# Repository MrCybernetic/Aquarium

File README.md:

# Aquarium
My overengineered aquarium

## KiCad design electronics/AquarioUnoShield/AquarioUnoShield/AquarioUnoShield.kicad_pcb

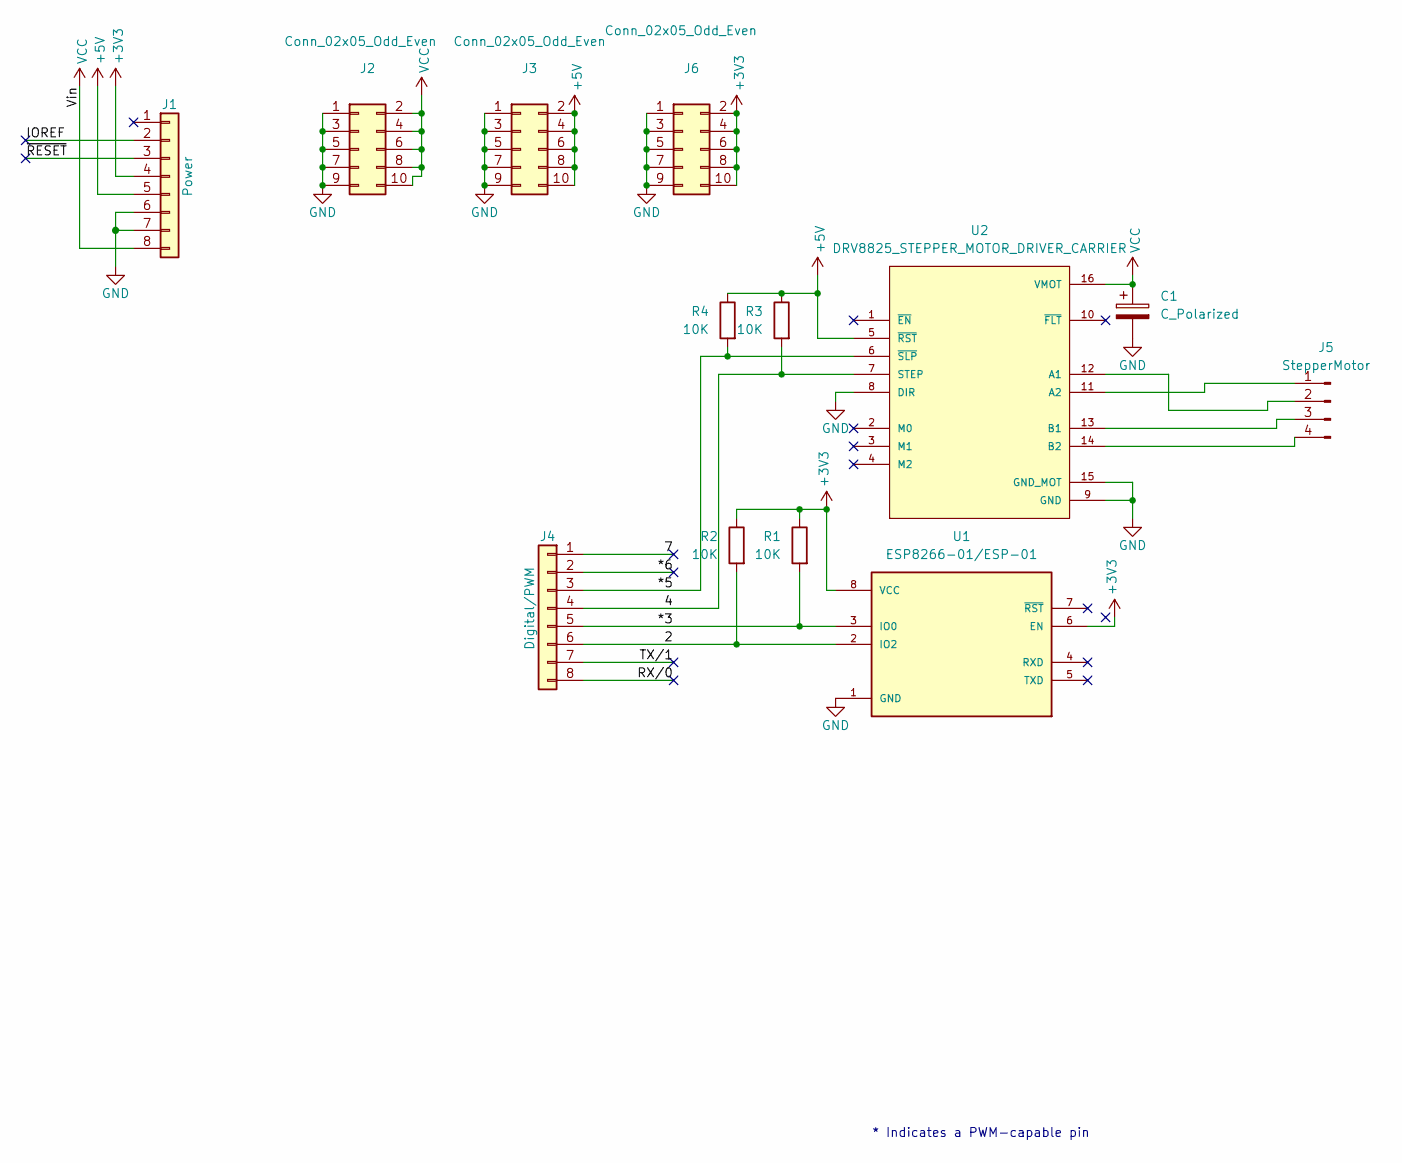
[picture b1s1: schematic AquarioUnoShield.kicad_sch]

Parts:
C1: C_Polarized; CP_Radial_D10.0mm_P5.00mm
J1: Power; PinSocket_1x08_P2.54mm_Vertical
J2, J3, J6: Conn_02x05_Odd_Even; PinSocket_2x05_P2.54mm_Vertical_aquario
J4: Digital/PWM; PinSocket_1x08_P2.54mm_Vertical
J5: StepperMotor; PinSocket_1x04_P2.54mm_Vertical
R1, R2, R3, R4: 10K; R_0402_1005Metric_Pad0.72x0.64mm_HandSolder
U1: ESP8266-01/ESP-01; XCVR_ESP8266-01_ESP-01; PARTREV V1.2
U2: DRV8825_STEPPER_MOTOR_DRIVER_CARRIER; IC_DRV8825_STEPPER_MOTOR_DRIVER_CARRIER

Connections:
+3V3: J1.4, J6.2, J6.4, J6.6, J6.8, J6.10, R1.1, R2.1, U1.6 (EN), U1.8 (VCC)
+5V: J1.5, J3.2, J3.4, J3.6, J3.8, J3.10, R3.1, R4.1, U2.5 (~RST)
/2: J4.6, R2.2, U1.2 (IO2)
/4: J4.4, R3.2, U2.7 (STEP)
/7: J4.1
/*3: J4.5, R1.2, U1.3 (IO0)
/*5: J4.3, R4.2, U2.6 (~SLP)
/*6: J4.2
/IOREF: J1.2
/RX/0: J4.8
/TX/1: J4.7
/~RESET: J1.3
GND: C1.2, J1.6, J1.7, J2.1, J2.3, J2.5, J2.7, J2.9, J3.1, J3.3, J3.5, J3.7, J3.9, J6.1, J6.3, J6.5, J6.7, J6.9, U1.1 (GND), U2.8 (DIR), U2.9 (GND), U2.15 (GND_MOT)
unnamed: J5.1, U2.11 (A2)
unnamed: J5.2, U2.12 (A1)
unnamed: J5.3, U2.13 (B1)
unnamed: J5.4, U2.14 (B2)
VCC: C1.1, J1.8, J2.2, J2.4, J2.6, J2.8, J2.10, U2.16 (VMOT)

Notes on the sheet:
* Indicates a PWM-capable pin

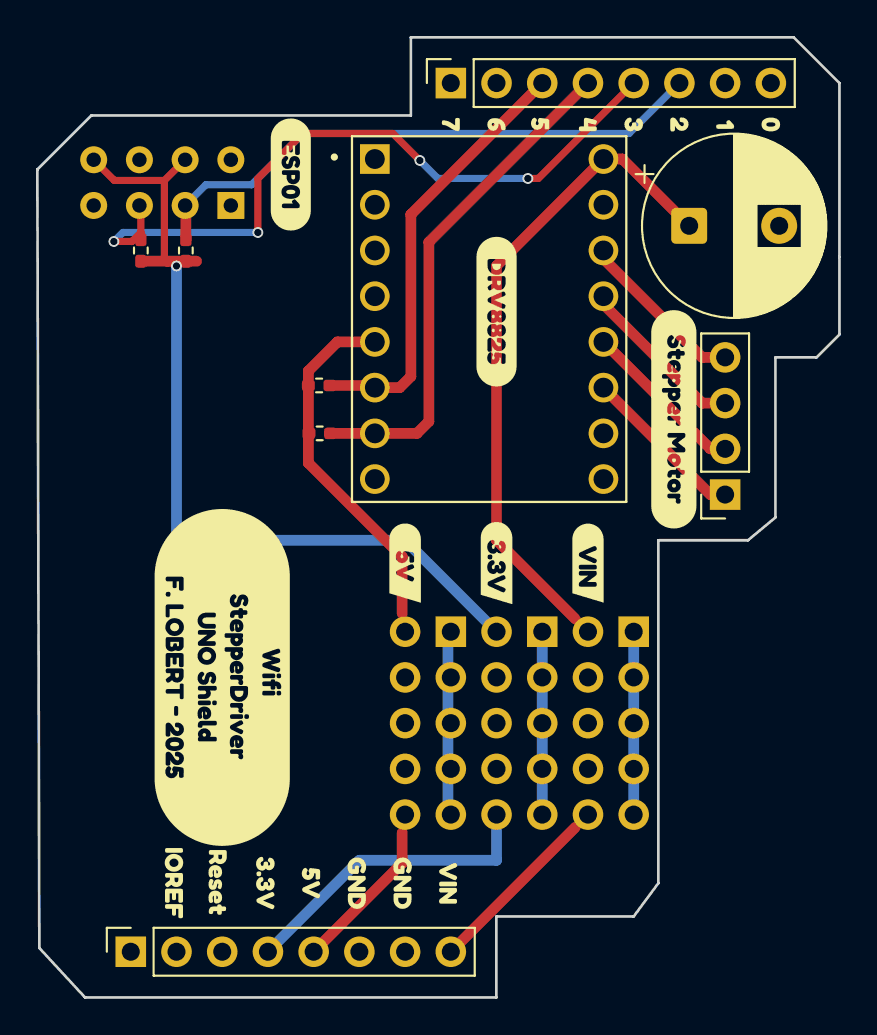
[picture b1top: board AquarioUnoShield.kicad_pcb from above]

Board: 2 copper layers, 44.6 x 53.3 mm, 35 parts (0 on the bottom side), 12 nets.

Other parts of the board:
kibuzzard-683C11A0: G***; kibuzzard-683C11A0
kibuzzard-683C11A6: G***; kibuzzard-683C11A6
kibuzzard-683C11AA: G***; kibuzzard-683C11AA
kibuzzard-683C11C1: G***; kibuzzard-683C11C1
kibuzzard-683C11D2: G***; kibuzzard-683C11D2
kibuzzard-683C11DA: G***; kibuzzard-683C11DA
kibuzzard-683C117F: G***; kibuzzard-683C117F
kibuzzard-683C119A: G***; kibuzzard-683C119A
kibuzzard-683C119D: G***; kibuzzard-683C119D
kibuzzard-683C145E: G***; kibuzzard-683C145E
kibuzzard-683C174A: G***; kibuzzard-683C174A
kibuzzard-683C175D: G***; kibuzzard-683C175D
kibuzzard-683C176E: G***; kibuzzard-683C176E
kibuzzard-683C584C: G***; kibuzzard-683C584C
kibuzzard-683C1190: G***; kibuzzard-683C1190
kibuzzard-683C1194: G***; kibuzzard-683C1194
kibuzzard-683C1411: G***; kibuzzard-683C1411
kibuzzard-683C1466: G***; kibuzzard-683C1466
kibuzzard-683C1752: G***; kibuzzard-683C1752
kibuzzard-683C1756: G***; kibuzzard-683C1756
kibuzzard-683C1766: G***; kibuzzard-683C1766
kibuzzard-683C1774: G***; kibuzzard-683C1774

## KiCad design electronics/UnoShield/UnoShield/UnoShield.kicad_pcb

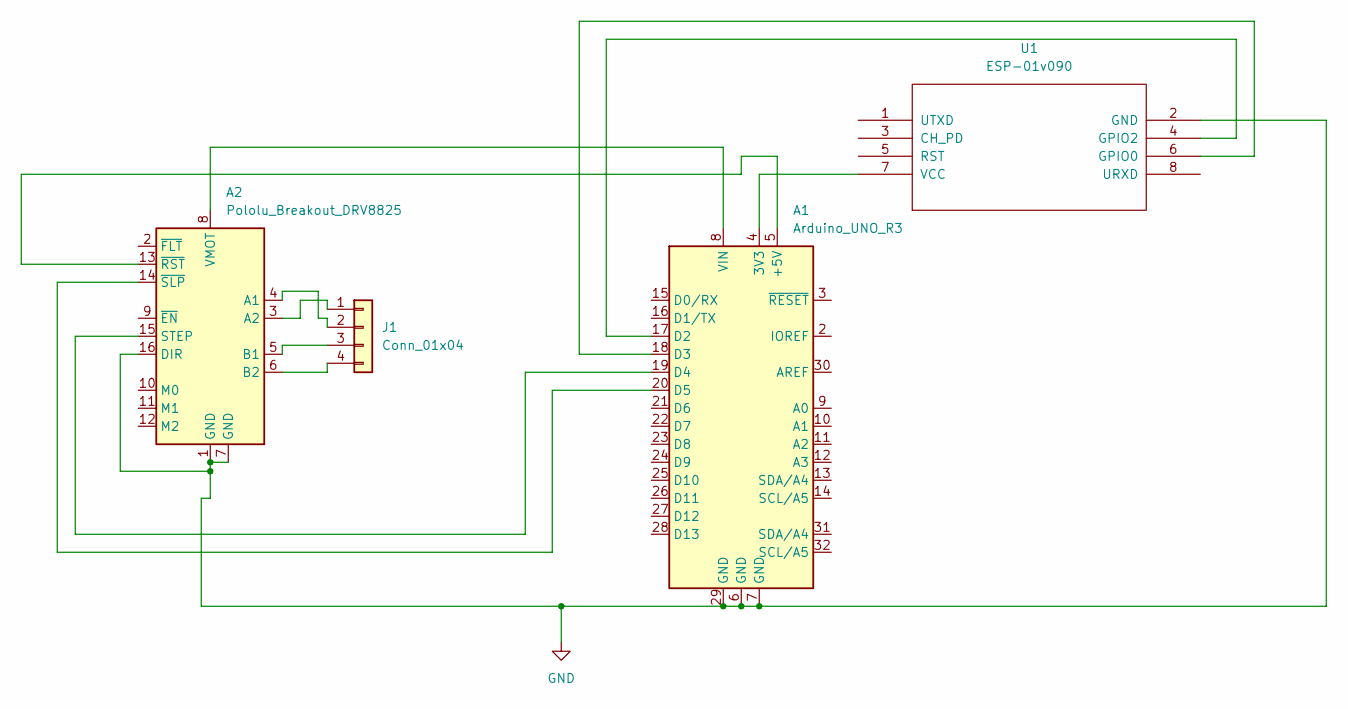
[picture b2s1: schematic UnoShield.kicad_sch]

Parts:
A1: Arduino_UNO_R3
A2: Pololu_Breakout_DRV8825; Pololu_Breakout-16_15.2x20.3mm
J1: Conn_01x04; PinSocket_1x04_P2.54mm_Vertical
U1: ESP-01v090; ESP-01

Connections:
GND: A1.6 (GND), A1.7 (GND), A1.29 (GND), A2.1 (GND), A2.7 (GND), A2.16 (DIR), U1.2 (GND)
unnamed: A1.4 (3V3), U1.7 (VCC)
unnamed: A1.5 (+5V), A2.13 (~RST)
unnamed: A1.17 (D2), U1.4 (GPIO2)
unnamed: A1.18 (D3), U1.6 (GPIO0)
unnamed: A1.19 (D4), A2.15 (STEP)
unnamed: A1.20 (D5), A2.14 (~SLP)
unnamed: A1.8 (VIN), A2.8 (VMOT)
unnamed: A2.4 (A1), J1.2
unnamed: A2.3 (A2), J1.1
unnamed: A2.5 (B1), J1.3
unnamed: A2.6 (B2), J1.4

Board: 2 copper layers, 4 parts (0 on the bottom side), 12 nets, no tracks yet.

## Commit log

2025-05-18 init
2025-05-18 Add gitignore and secrets template
2025-06-08 add electronics
2025-06-30 Refactor code structure for improved readability and maintainability
2025-06-30 Remove StepperDriverMiniPro and testdrv8825 files
